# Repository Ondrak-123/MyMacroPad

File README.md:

# MyMacroPad
"MyMacroPad" with 9 keys and an encoder, oled screen and backlight .

The 3D files might slightly change in the future.

Here is the list of all the components you need:

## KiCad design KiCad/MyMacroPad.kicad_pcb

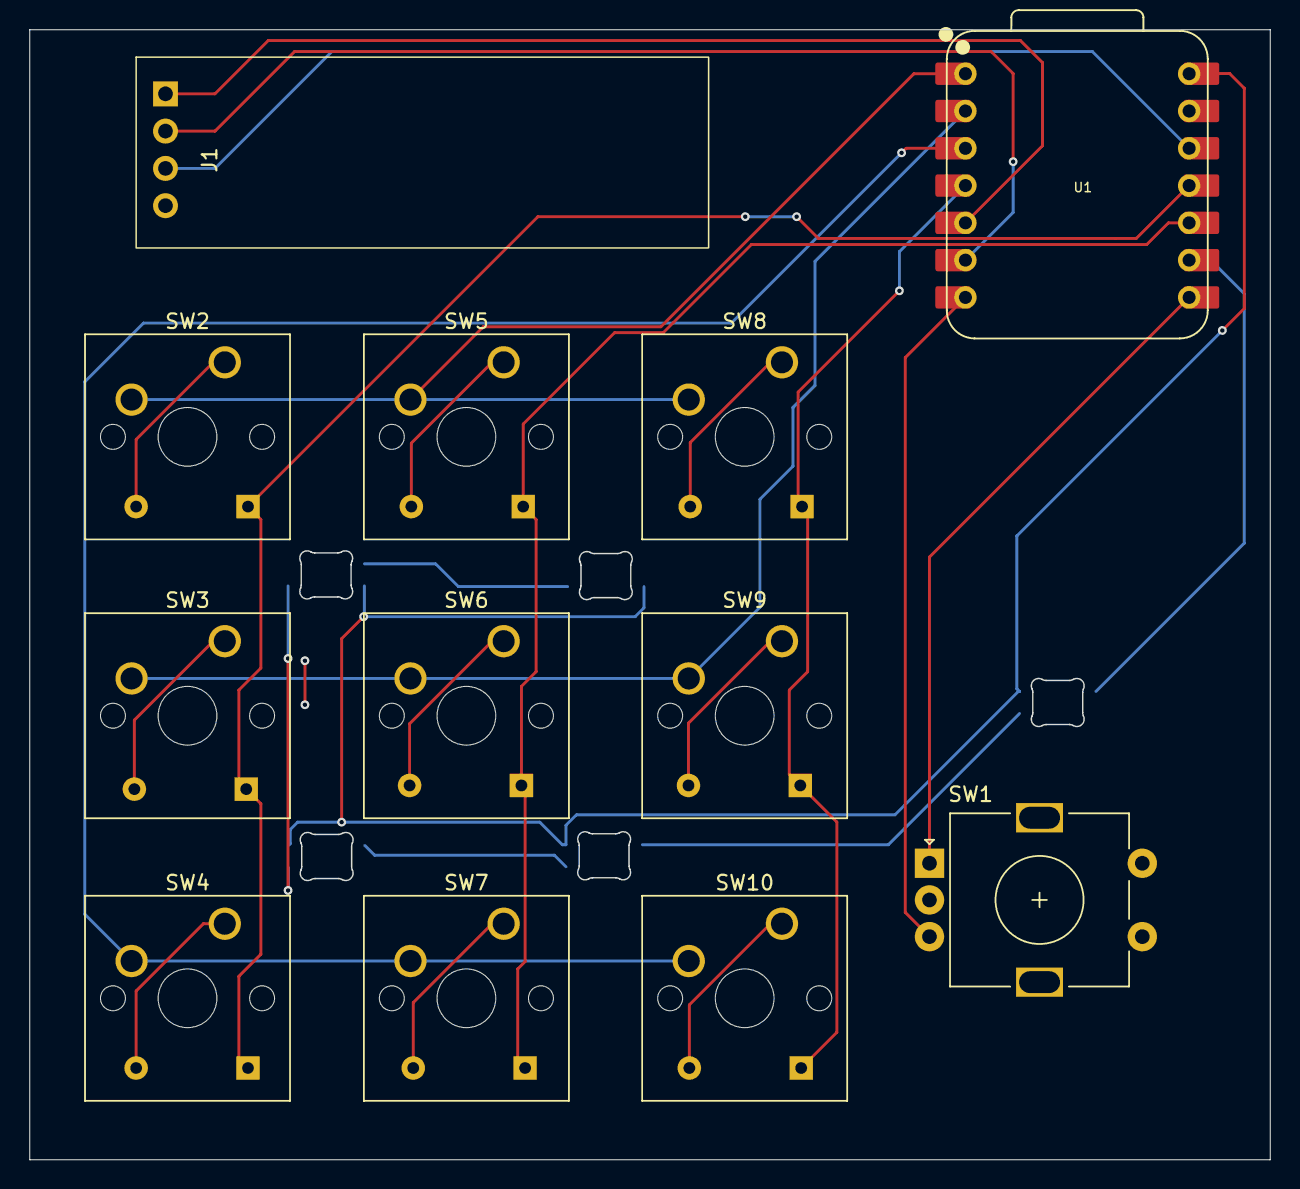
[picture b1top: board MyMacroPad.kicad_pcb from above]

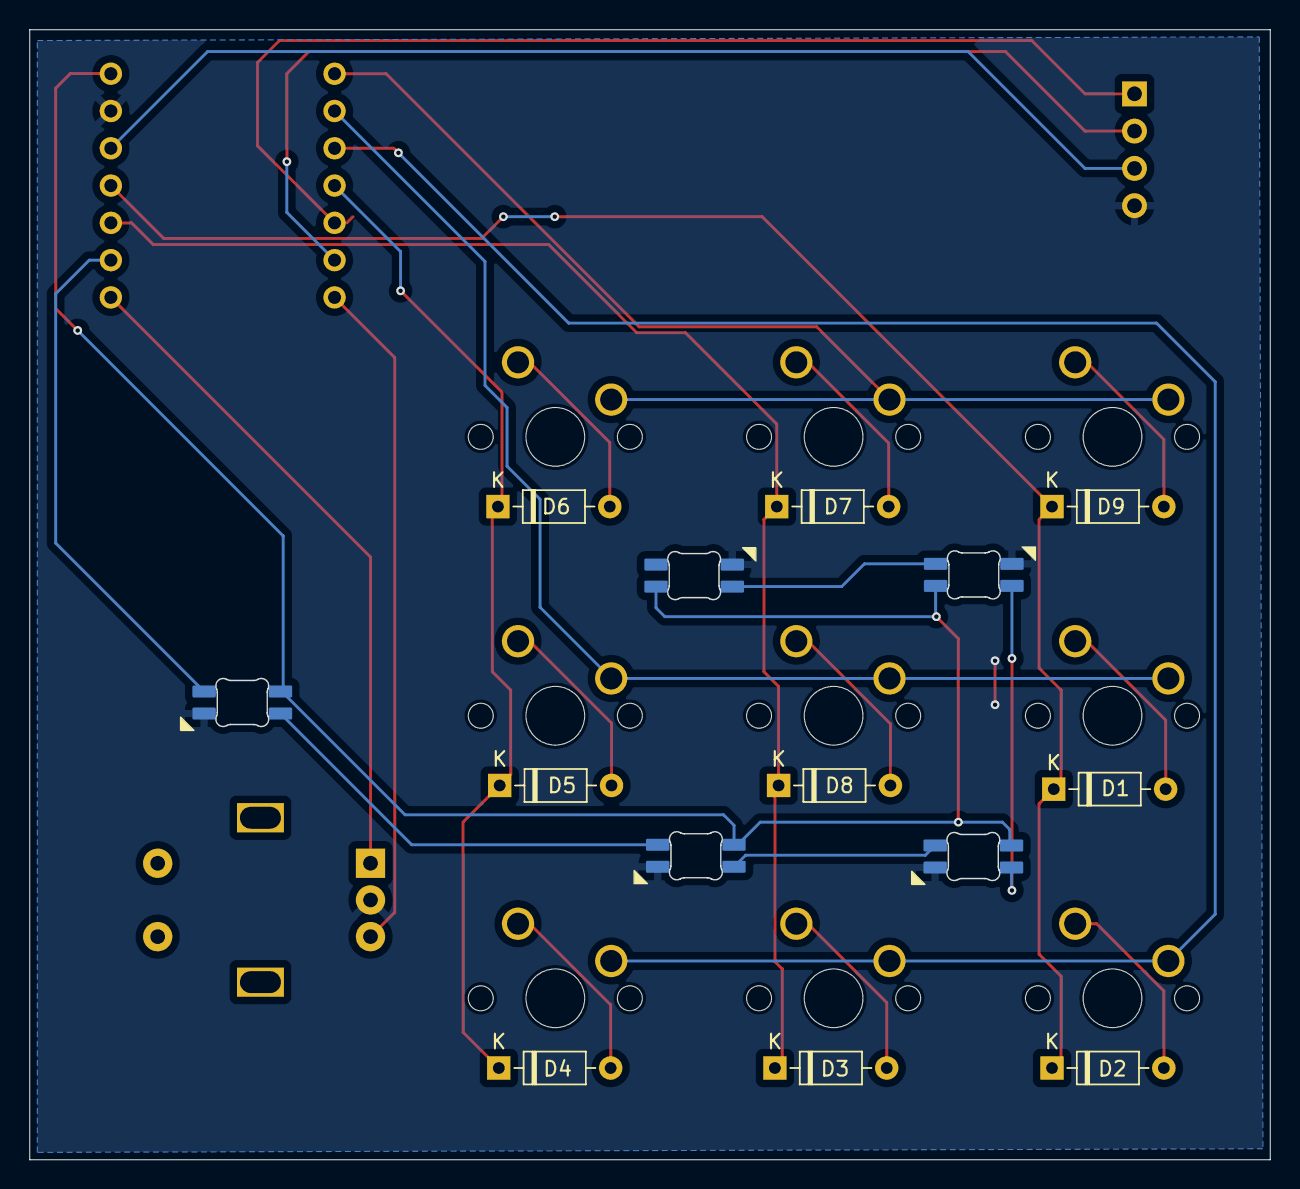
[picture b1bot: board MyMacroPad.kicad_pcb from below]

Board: 2 copper layers, 84.5 x 76.9 mm, 26 parts (9 on the bottom side), 27 nets.

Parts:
D1, D2, D3, D4, D5, D6, D7, D8, D9: 1N4148; D_DO-35_SOD27_P7.62mm_Horizontal
D16, D16#2, D16#3, D16#4, D16#5: SK6812MINI; MX_SK6812MINI-E_REV
J1: OLED; PinHeader_1x04_P2.54mm_Vertical
SW1: RotaryEncoder_Switch; RotaryEncoder_Alps_EC11E-Switch_Vertical_H20mm
SW2, SW3, SW4, SW5, SW6, SW7, SW8, SW9, SW10: SW_Push; SW_Cherry_MX_1.00u_PCB
U1: XIAO-RP2040-DIP

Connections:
3V3: J1.3, U1.12 (3V3)
5V: D16.1 (DOUT), D16#2.1 (DOUT), D16#3.1 (DOUT), D16#4.1 (DOUT), D16#5.1 (DOUT), U1.14 (VBUS)
C1: SW2.2, SW5.2, SW8.2, U1.1 (GPIO26/ADC0/A0)
C2: SW3.2, SW6.2, SW9.2, U1.2 (GPIO27/ADC1/A1)
C3: SW4.2, SW7.2, SW10.2, U1.3 (GPIO28/ADC2/A2)
GND: D16.3 (DIN), D16#2.3 (DIN), D16#3.3 (DIN), D16#4.3 (DIN), D16#5.3 (DIN), J1.4, SW1.C, U1.13 (GND)
GPIO0: SW1.B, U1.7 (GPIO0/TX)
GPIO1: SW1.A, U1.8 (GPIO1/RX)
unnamed: D1.2 (A), SW3.1
unnamed: D2.2 (A), SW4.1
unnamed: D3.2 (A), SW7.1
unnamed: D4.2 (A), SW10.1
unnamed: D5.2 (A), SW9.1
unnamed: D6.2 (A), SW8.1
unnamed: D7.2 (A), SW5.1
unnamed: D8.2 (A), SW6.1
unnamed: D9.2 (A), SW2.1
unnamed: D16#2.4 (VDD), D16#4.2 (VSS)
unnamed: D16#2.2 (VSS), D16#3.4 (VDD)
unnamed: D16#3.2 (VSS), D16#5.4 (VDD)
unnamed: D16.4 (VDD), D16#5.2 (VSS)
R1: D1.1 (K), D2.1 (K), D9.1 (K), U1.11 (GPIO3/MOSI)
R2: D3.1 (K), D7.1 (K), D8.1 (K), U1.10 (GPIO4/MISO)
R3: D4.1 (K), D5.1 (K), D6.1 (K), U1.4 (GPIO29/ADC3/A3)
SCK: D16#4.4 (VDD), U1.9 (GPIO2/SCK)
SCL: J1.2, U1.6 (GPIO7/SCL)
SDA: J1.1, U1.5 (GPIO6/SDA)

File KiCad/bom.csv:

Designator,Footprint,Quantity,Value,LCSC Part #
"D1, D2, D3, D4, D5, D6, D7, D8, D9",D_DO-35_SOD27_P7.62mm_Horizontal,9,1N4148,
"D16_5, D16_4, D16_3, D16_2, D16",MX_SK6812MINI-E_REV,5,SK6812MINI,
J1,PinHeader_1x04_P2.54mm_Vertical,1,OLED,
SW1,RotaryEncoder_Alps_EC11E-Switch_Vertical_H20mm,1,RotaryEncoder_Switch,
"SW10, SW2, SW3, SW4, SW5, SW6, SW7, SW8, SW9",SW_Cherry_MX_1.00u_PCB,9,SW_Push,
U1,XIAO-RP2040-DIP,1,XIAO-RP2040-DIP,

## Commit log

2026-01-30 Create -
2026-02-01 Add image to README for visualization
    Added an image to the README for better visualization.
2026-02-04 Add keyboard setup with RGB, encoder, and OLED
2026-02-04 Add initial readme for XIAO SEED RP2040 project
2026-02-04 Update code.py
    Some small changes.
2026-02-04 Code
2026-02-05 Update README.md
    Added multiple images to the README for better visualization.
2026-02-05 Bug fix
2026-02-06 Update README with components list and images
    Added a list of required components with images.
2026-02-06 Add components list to README
    Added a section listing required components.
2026-02-06 Add new component image to README
    Added an additional image to the components list in the README.
2026-02-07 Create A
2026-02-07 Add new images to README
2026-02-07 pinout change
2026-03-05 Better images
2026-03-05 Create KiCad
2026-03-05 Revise README.md project description
    Updated project description and removed unnecessary lines.
